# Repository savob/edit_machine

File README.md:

# Edit Machine

A hardware based goal tracker I made for a friend. The goal was simple: have buttons that illuminate LEDs to mark off completed tasks, another LED to flash when all goals are marked off, and to top it all off - a reset switch.

One requirement that was imposed on the project was that **we were to exclusively use material I already had laying about my apartment**, ideally reusing parts harvested off of other circuit boards I kept around for this purpose. 

Mechanically, there was a desire to have a space between the buttons and LEDs to record the goals corresponding to each row.

# Outcome

The final circuit was soldered on a perf(erated) board, which after *much* debugging made me long for a custom circuit board! It would probably surprize no one that this did not work on the first try. I'm relieved and a wee bit stupified that we didn't actually fry any chips in the process.

By placing the chips in the middle I naturally created a space for the goals to be recorded inbetween the LEDs and the buttons. The chip cases can even act as fairly even supports for the writing pad above. *Note: that capacitor in the middle was bent down after the picture was taken.*

# The Circuitry

Originally I was planning to use some basic OR logic chips feeding into themselves to act as the toggles for the LEDs, however the chips I had were incorrectly labelled and were in fact XORs. So I ended up using some 556 timer chips as RS flip-flops for this instead. The driving for the final LED when all the goals are complete was accomplished using a chain of ANDs to combine the outputs for all the LEDs to enable the remaining timer in the 556's.

I have made a preliminary custom circuit board which is a rough proxy of what the prototype was and is included as part of this project. Although it will function, it's dimesions and arrangement may change before I commit to having it made.

## Software Used

The circuit files were initially prepared in KiCad 7.0.5.

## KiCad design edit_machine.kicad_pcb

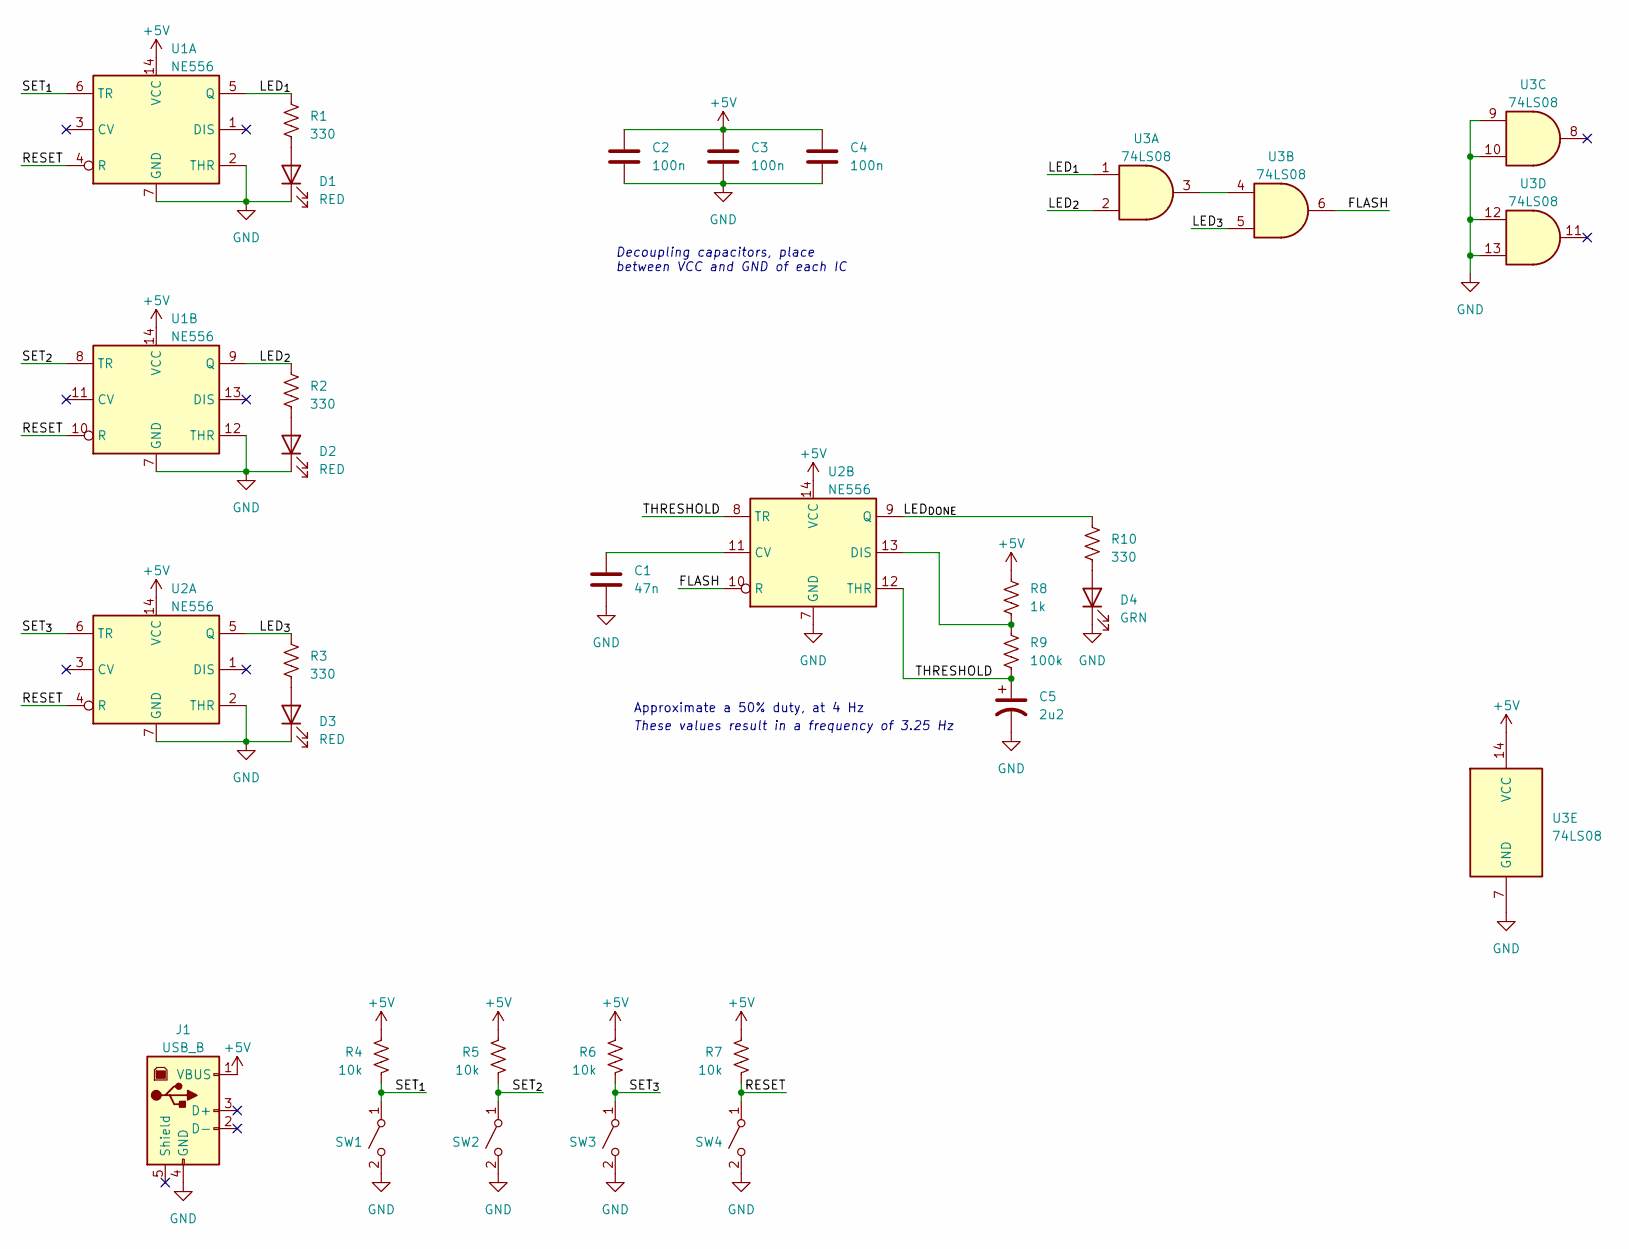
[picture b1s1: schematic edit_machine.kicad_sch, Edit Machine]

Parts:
C1: 47n; C_Disc_D3.4mm_W2.1mm_P2.50mm
C2, C3, C4: 100n; C_Disc_D3.8mm_W2.6mm_P2.50mm
C5: 2u2; CP_Radial_D4.0mm_P2.00mm
D1, D2, D3: RED; LED_D4.0mm
D4: GRN; LED_D4.0mm
J1: USB_B; USB_B_OST_USB-B1HSxx_Horizontal
R1, R2, R3, R10: 330; R_Axial_DIN0207_L6.3mm_D2.5mm_P7.62mm_Horizontal
R4, R5, R6, R7: 10k; R_Axial_DIN0207_L6.3mm_D2.5mm_P7.62mm_Horizontal
R8: 1k; R_Axial_DIN0207_L6.3mm_D2.5mm_P7.62mm_Horizontal
R9: 100k; R_Axial_DIN0207_L6.3mm_D2.5mm_P7.62mm_Horizontal
SW1, SW2, SW3, SW4: SW_SPST; SW_PUSH_6mm_H5mm
U1, U2: NE556; DIP-14_W7.62mm
U3: 74LS08; DIP-14_W7.62mm

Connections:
+5V: C2.1, C3.1, C4.1, J1.1 (VBUS), R4.1, R5.1, R6.1, R7.1, R8.1, U1.14 (VCC), U2.14 (VCC), U3.14 (VCC)
/FLASH: U2.10 (R), U3.6
/LED_{1}: R1.1, U1.5 (Q), U3.1
/LED_{2}: R2.1, U1.9 (Q), U3.2
/LED_{3}: R3.1, U2.5 (Q), U3.5
/LED_{DONE}: R10.1, U2.9 (Q)
/RESET: R7.2, SW4.1 (A), U1.4 (R), U1.10 (R), U2.4 (R)
/SET_{1}: R4.2, SW1.1 (A), U1.6 (TR)
/SET_{2}: R5.2, SW2.1 (A), U1.8 (TR)
/SET_{3}: R6.2, SW3.1 (A), U2.6 (TR)
/THRESHOLD: C5.1, R9.2, U2.8 (TR), U2.12 (THR)
GND: C1.2, C2.2, C3.2, C4.2, C5.2, D1.1 (K), D2.1 (K), D3.1 (K), D4.1 (K), J1.4 (GND), SW1.2 (B), SW2.2 (B), SW3.2 (B), SW4.2 (B), U1.2 (THR), U1.7 (GND), U1.12 (THR), U2.2 (THR), U2.7 (GND), U3.7 (GND), U3.9, U3.10, U3.12, U3.13
unnamed: D1.2 (A), R1.2
unnamed: D2.2 (A), R2.2
unnamed: D3.2 (A), R3.2
unnamed: D4.2 (A), R10.2
unnamed: C1.1, U2.11 (CV)
unnamed: R8.2, R9.1, U2.13 (DIS)
unnamed: U3.3, U3.4

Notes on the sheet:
Approximate a 50% duty, at 4 Hz
Decoupling capacitors, place between VCC and GND of each IC
These values result in a frequency of 3.25 Hz

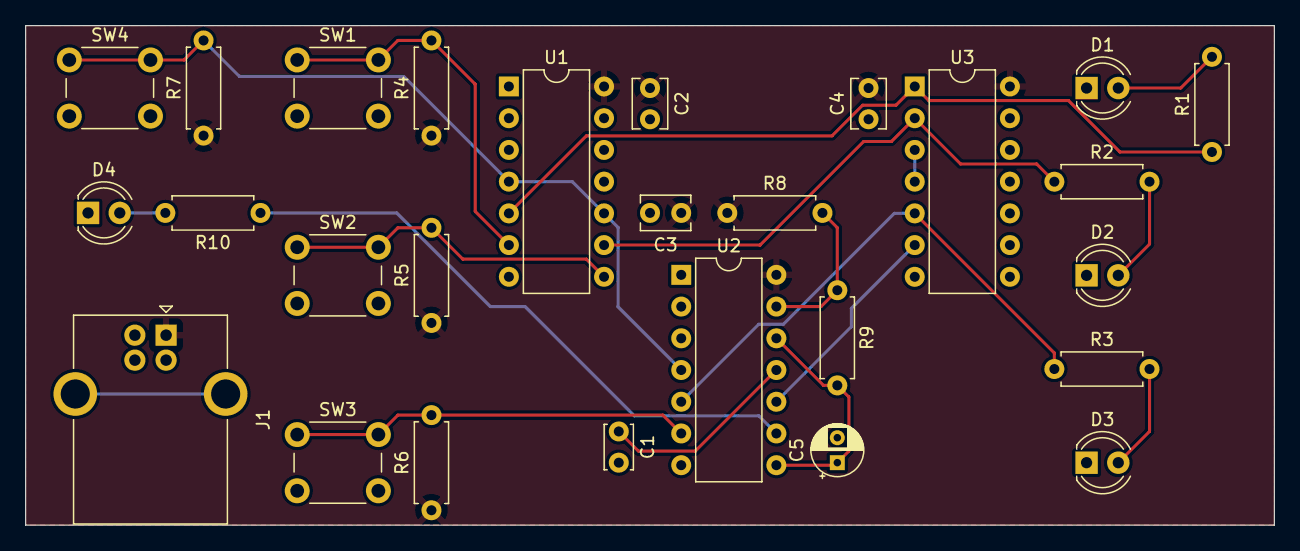
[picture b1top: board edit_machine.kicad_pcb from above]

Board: 2 copper layers, 100.0 x 40.0 mm, 27 parts (0 on the bottom side), 19 nets.

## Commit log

2023-07-18 Upload of design files
2023-07-18 Wrote proper readme
2023-07-18 Updated SVG for schematic
2024-01-04 Added licence
